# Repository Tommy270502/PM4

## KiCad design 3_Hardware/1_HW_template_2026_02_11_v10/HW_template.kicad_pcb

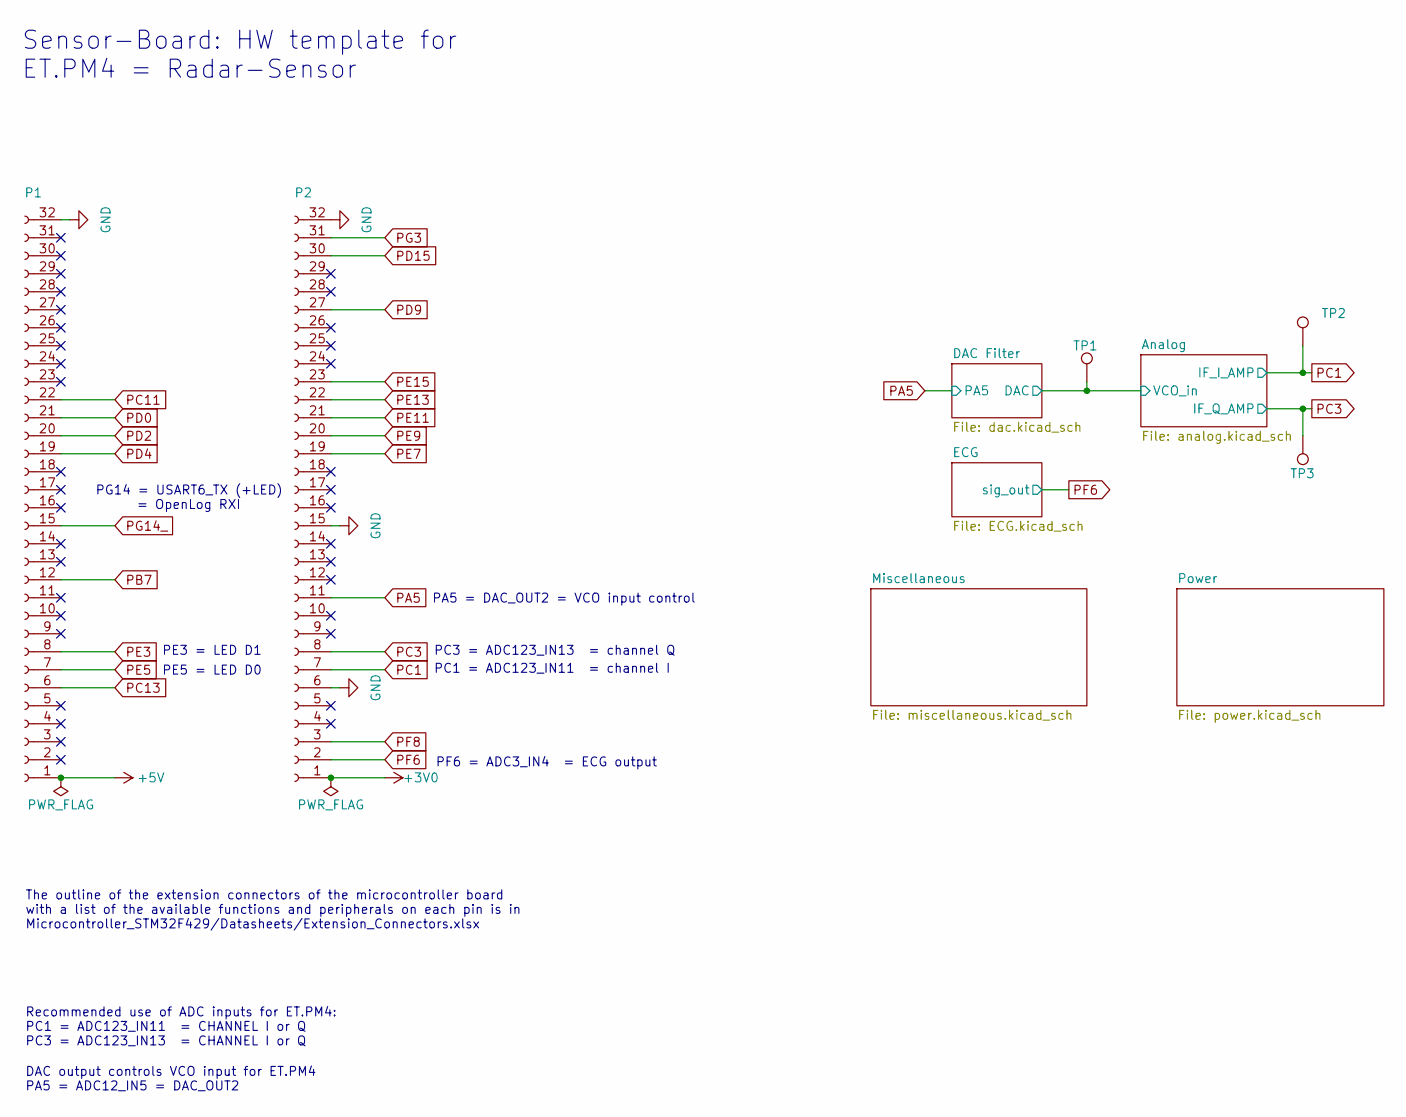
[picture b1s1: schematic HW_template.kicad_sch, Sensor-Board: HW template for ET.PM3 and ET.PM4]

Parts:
P1, P2: Conn_01x32_Female; PinSocket_1x32_P2.54mm_Vertical
TP1, TP2, TP3: TestPoint_Loop_D2.60mm_Drill1.6mm_Beaded

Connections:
+3V0: P2.1
+5V: P1.1; also elsewhere on the board
/Analog/VCO_in: TP1.1; also elsewhere on the board
GND: P1.32, P2.6, P2.15, P2.32; also elsewhere on the board
PA5: P2.11; also elsewhere on the board
PB7: P1.12
PC1: P2.7, TP2.1; also elsewhere on the board
PC3: P2.8, TP3.1; also elsewhere on the board
PC11: P1.22
PC13: P1.6
PD0: P1.21
PD2: P1.20
PD4: P1.19
PD9: P2.27
PD15: P2.30
PE3: P1.8; also elsewhere on the board
PE5: P1.7; also elsewhere on the board
PE7: P2.19
PE9: P2.20
PE11: P2.21
PE13: P2.22
PE15: P2.23
PF6: P2.2; also elsewhere on the board
PF8: P2.3
PG3: P2.31
PG14_: P1.15; also elsewhere on the board

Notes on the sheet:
The outline of the extension connectors of the microcontroller board with a list of the available functions and peripherals on each pin is in Microcontroller_STM32F429/Datasheets/Extension_Connectors.xlsx
PA5 = DAC_OUT2 = VCO input control
PG14 = USART6_TX (+LED) = OpenLog RXI
PC3 = ADC123_IN13 = channel Q
DAC output controls VCO input for ET.PM4 PA5 = ADC12_IN5 = DAC_OUT2
PF6 = ADC3_IN4 = ECG output
PE5 = LED D0
Recommended use of ADC inputs for ET.PM4: PC1 = ADC123_IN11 = CHANNEL I or Q PC3 = ADC123_IN13 = CHANNEL I or Q
PC1 = ADC123_IN11 = channel I
Sensor-Board: HW template for ET.PM4 = Radar-Sensor
PE3 = LED D1

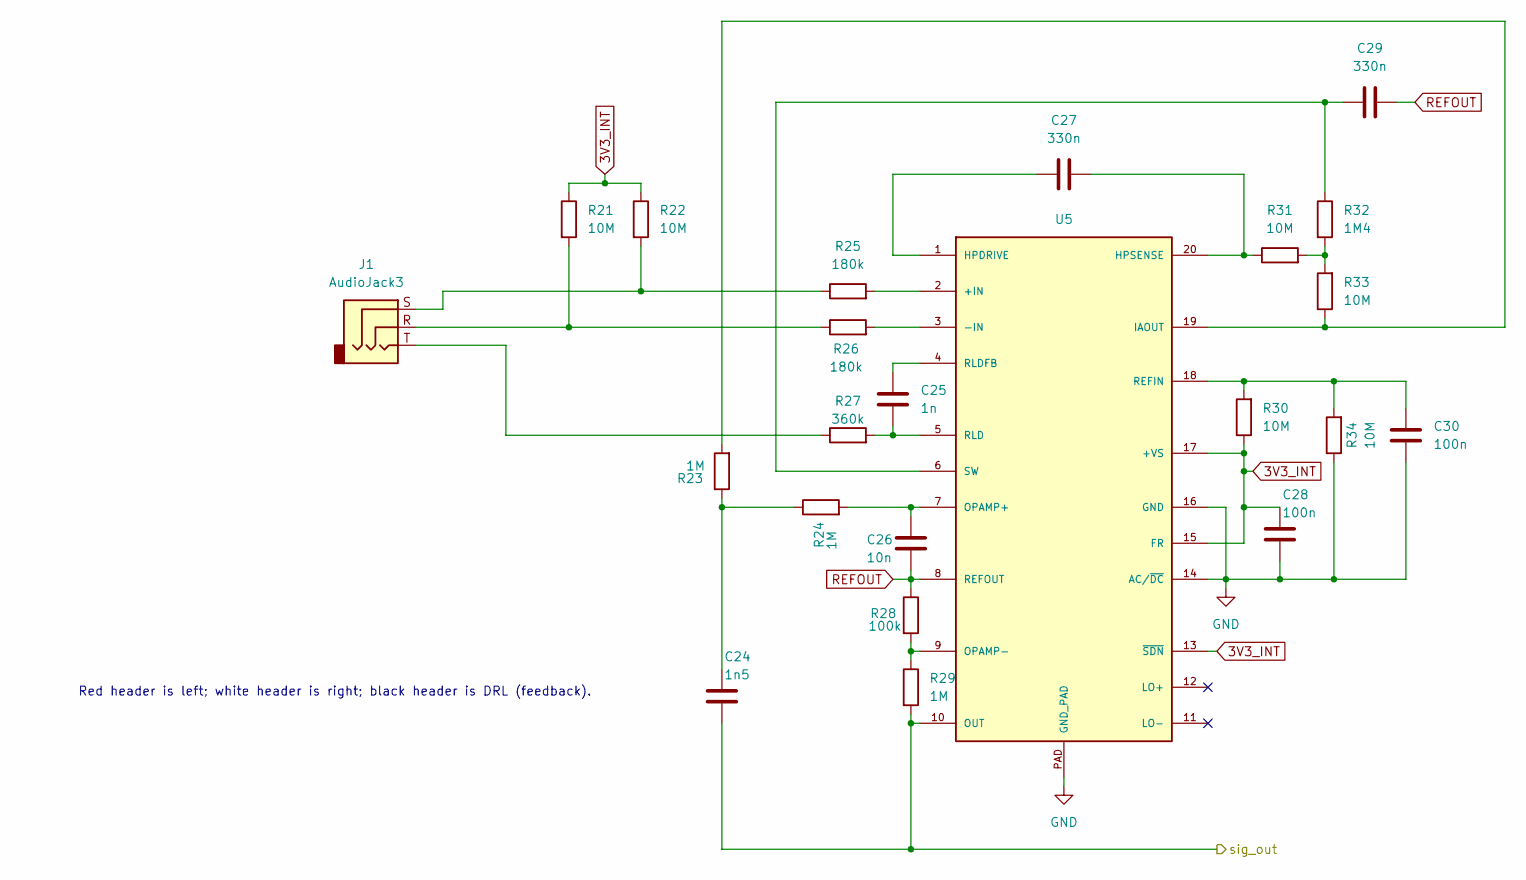
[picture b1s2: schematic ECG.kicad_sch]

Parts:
C24: 1n5; C_0603_1608Metric_Pad1.08x0.95mm_HandSolder
C25: 1n; C_0603_1608Metric_Pad1.08x0.95mm_HandSolder
C26: 10n; C_0603_1608Metric_Pad1.08x0.95mm_HandSolder
C27, C29: 330n; C_0603_1608Metric_Pad1.08x0.95mm_HandSolder
C28, C30: 100n; C_0603_1608Metric_Pad1.08x0.95mm_HandSolder
J1: AudioJack3; Jack_3.5mm_CUI_SJ-3523-SMT_Horizontal
R21, R22, R30, R31, R33, R34: 10M; R_0603_1608Metric_Pad0.98x0.95mm_HandSolder
R23, R24, R29: 1M; R_0603_1608Metric_Pad0.98x0.95mm_HandSolder
R25, R26: 180k; R_0603_1608Metric_Pad0.98x0.95mm_HandSolder
R27: 360k; R_0603_1608Metric_Pad0.98x0.95mm_HandSolder
R28: 100k; R_0603_1608Metric_Pad0.98x0.95mm_HandSolder
R32: 1M4; R_0603_1608Metric_Pad0.98x0.95mm_HandSolder
U5: AD8232ACPZ-R7; LFCSP_20

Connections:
3V3_INT: C28.2, R21.1, R22.1, R30.1, U5.13 (~SDN), U5.15 (FR), U5.17 (+VS); also elsewhere on the board
GND: C28.1, C30.1, R34.1, U5.14 (AC/~DC), U5.16 (GND), U5.PAD (GND_PAD); also elsewhere on the board
unnamed: C24.2, R23.1, R24.1
unnamed: J1.R, R21.2, R26.1
unnamed: J1.S, R22.2, R25.1
unnamed: J1.T, R27.1
unnamed: R31.2, R32.2, R33.2
unnamed: R25.2, U5.2 (+IN)
unnamed: R26.2, U5.3 (-IN)
unnamed: C27.1, U5.1 (HPDRIVE)
unnamed: C27.2, R31.1, U5.20 (HPSENSE)
unnamed: R23.2, R33.1, U5.19 (IAOUT)
unnamed: C26.2, R24.2, U5.7 (OPAMP+)
unnamed: R28.2, R29.1, U5.9 (OPAMP-)
unnamed: C30.2, R30.2, R34.2, U5.18 (REFIN)
unnamed: C25.2, R27.2, U5.5 (RLD)
unnamed: C25.1, U5.4 (RLDFB)
unnamed: C29.1, R32.1, U5.6 (SW)
PF6: C24.1, R29.2, U5.10 (OUT); also elsewhere on the board
REFOUT: C26.1, C29.2, R28.1, U5.8 (REFOUT)

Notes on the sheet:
Red header is left; white header is right; black header is DRL (feedback).

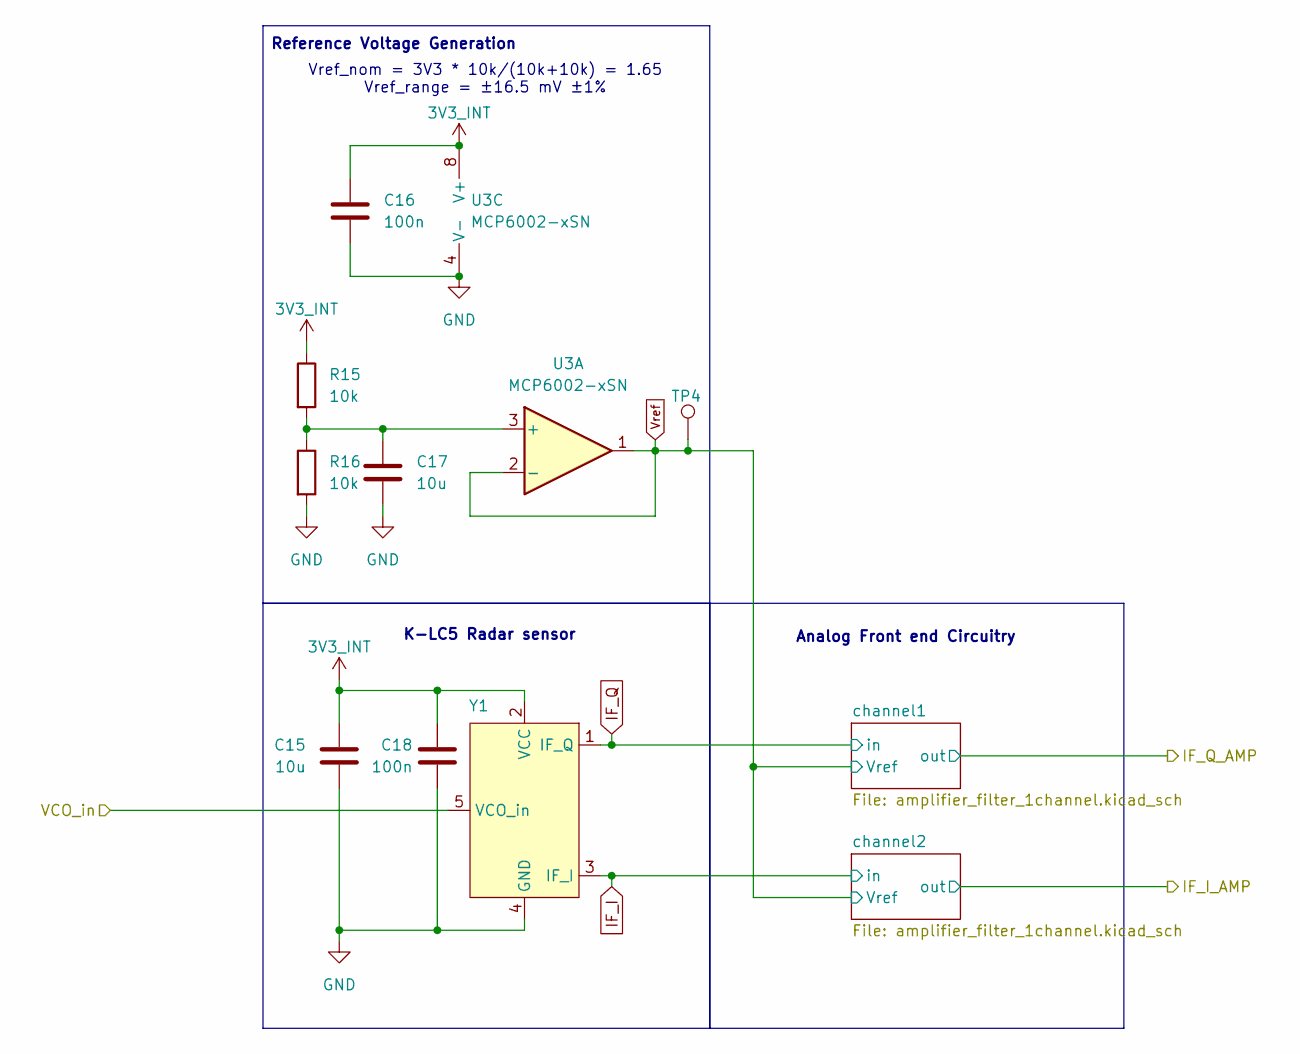
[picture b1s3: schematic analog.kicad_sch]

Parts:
C15, C17: 10u; C_0603_1608Metric_Pad1.08x0.95mm_HandSolder
C16, C18: 100n; C_0603_1608Metric_Pad1.08x0.95mm_HandSolder
R15, R16: 10k; R_0603_1608Metric_Pad0.98x0.95mm_HandSolder
TP4: TestPoint_Loop_D2.60mm_Drill1.6mm_Beaded
U3: MCP6002-xSN; SOIC-8_3.9x4.9mm_P1.27mm
Y1: Radar K-LC5-RFB-00C; Radar_K-LC5

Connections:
3V3_INT: C15.1, C16.1, C18.1, R15.1, U3.8 (V+), Y1.2 (VCC); also elsewhere on the board
/Analog/VCO_in: Y1.5 (VCO_in); also elsewhere on the board
GND: C15.2, C16.2, C17.2, C18.2, R16.2, U3.4 (V-), Y1.4 (GND); also elsewhere on the board
IF_I: Y1.3 (IF_I); also elsewhere on the board
IF_Q: Y1.1 (IF_Q); also elsewhere on the board
unnamed: C17.1, R15.2, R16.1, U3.3 (+)
Vref: TP4.1, U3.1, U3.2 (-); also elsewhere on the board

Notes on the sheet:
Analog Front end Circuitry
Reference Voltage Generation
K-LC5 Radar sensor
Vref_nom = 3V3 * 10k/(10k+10k) = 1.65 Vref_range = ±16.5 mV ±1%

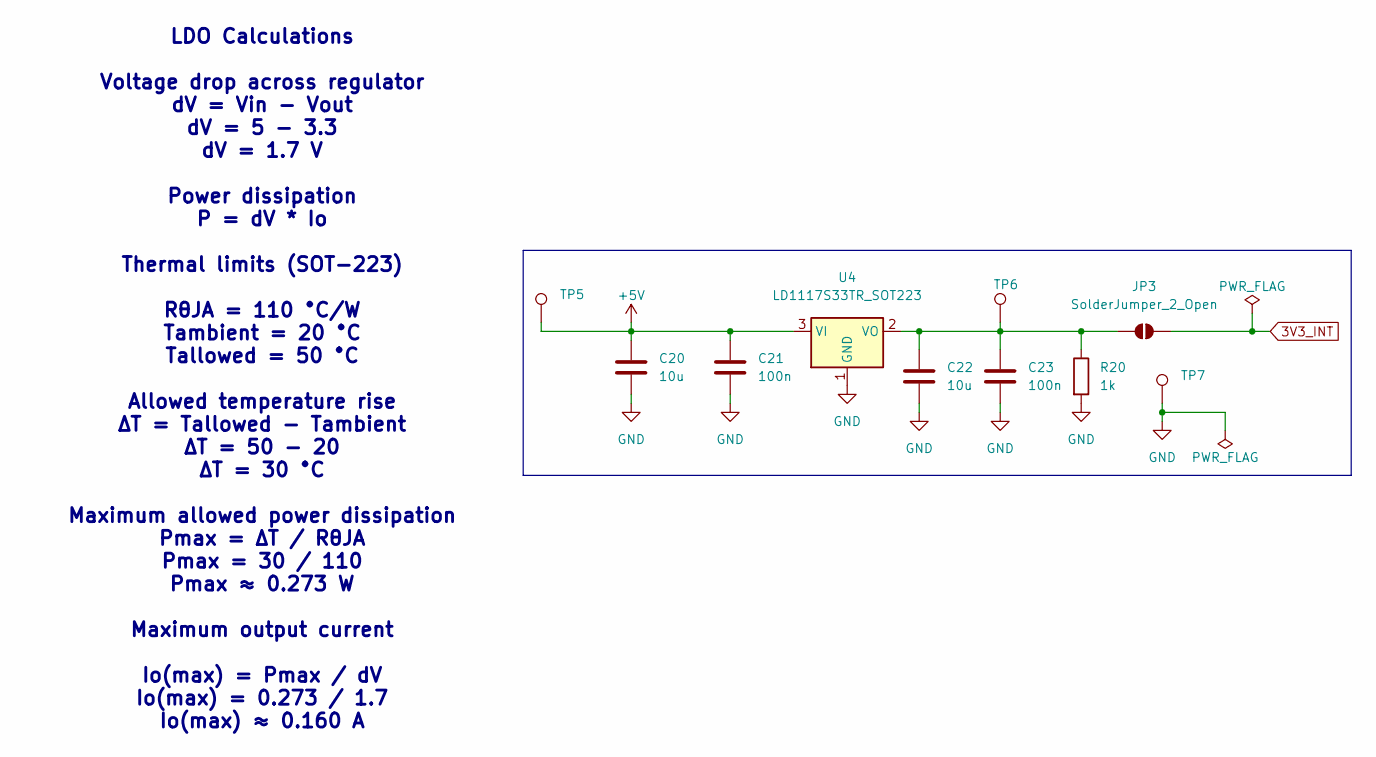
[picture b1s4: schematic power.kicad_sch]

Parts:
C20, C22: 10u; C_0805_2012Metric_Pad1.18x1.45mm_HandSolder
C21, C23: 100n; C_0805_2012Metric_Pad1.18x1.45mm_HandSolder
JP3: SolderJumper_2_Open; SolderJumper-2_P1.3mm_Open_RoundedPad1.0x1.5mm
R20: 1k; R_0805_2012Metric_Pad1.20x1.40mm_HandSolder
TP5, TP6, TP7: TestPoint_Loop_D2.60mm_Drill1.6mm_Beaded
U4: LD1117S33TR_SOT223; SOT-223-3_TabPin2

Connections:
3V3_INT: JP3.2 (B); also elsewhere on the board
+5V: C20.1, C21.1, TP5.1, U4.3 (VI); also elsewhere on the board
GND: C20.2, C21.2, C22.2, C23.2, R20.2, TP7.1, U4.1 (GND); also elsewhere on the board
unnamed: C22.1, C23.1, JP3.1 (A), R20.1, TP6.1, U4.2 (VO)

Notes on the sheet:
LDO Calculations Voltage drop across regulator dV = Vin - Vout dV = 5 - 3.3 dV = 1.7 V Power dissipation P = dV * Io Thermal limits (SOT-223) RθJA = 110 °C/W Tambient = 20 °C Tallowed = 50 °C Allowed temperature rise ΔT = Tallowed - Tambient ΔT = 50 - 20 ΔT = 30 °C Maximum allowed power dissipation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

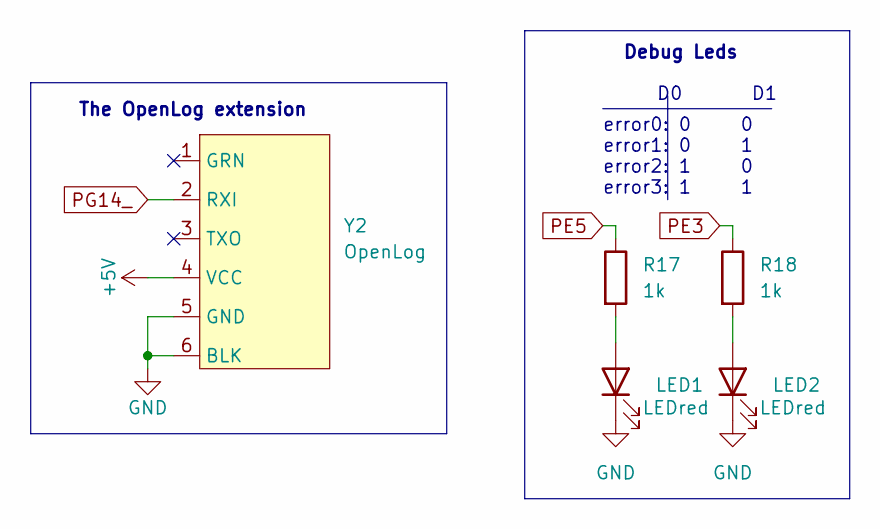
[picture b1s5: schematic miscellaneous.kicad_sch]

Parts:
LED1, LED2: LEDred; LED_0603_1608Metric_Pad1.05x0.95mm_HandSolder
R17, R18: 1k; R_0603_1608Metric_Pad0.98x0.95mm_HandSolder
Y2: OpenLog; PinSocket_1x06_P2.54mm_Vertical

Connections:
+5V: Y2.4 (VCC); also elsewhere on the board
GND: LED1.1 (K), LED2.1 (K), Y2.5 (GND), Y2.6 (BLK); also elsewhere on the board
unnamed: LED1.2 (A), R17.2
unnamed: LED2.2 (A), R18.2
PE3: R18.1; also elsewhere on the board
PE5: R17.1; also elsewhere on the board
PG14_: Y2.2 (RXI); also elsewhere on the board

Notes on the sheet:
error0: 0 0 error1: 0 1 error2: 1 0 error3: 1 1
The OpenLog extension
D0 D1
Debug Leds

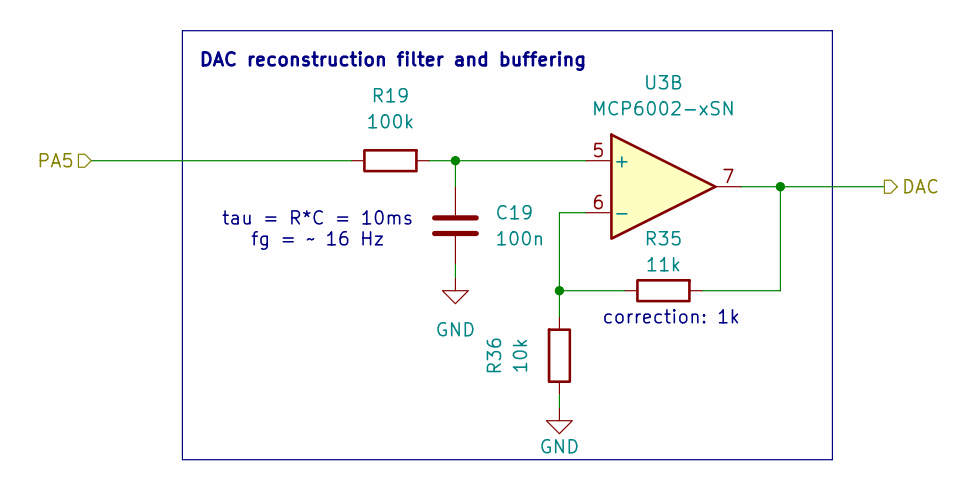
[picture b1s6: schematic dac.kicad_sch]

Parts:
C19: 100n; C_0603_1608Metric_Pad1.08x0.95mm_HandSolder
R19: 100k; R_0603_1608Metric_Pad0.98x0.95mm_HandSolder
R35: 11k; R_0603_1608Metric_Pad0.98x0.95mm_HandSolder
R36: 10k; R_0603_1608Metric_Pad0.98x0.95mm_HandSolder
U3: MCP6002-xSN; SOIC-8_3.9x4.9mm_P1.27mm

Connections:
/Analog/VCO_in: R35.2, U3.7; also elsewhere on the board
GND: C19.2, R36.1; also elsewhere on the board
unnamed: C19.1, R19.2, U3.5 (+)
unnamed: R35.1, R36.2, U3.6 (-)
PA5: R19.1; also elsewhere on the board

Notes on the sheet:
DAC reconstruction filter and buffering
correction: 1k
tau = R*C = 10ms fg = ~ 16 Hz

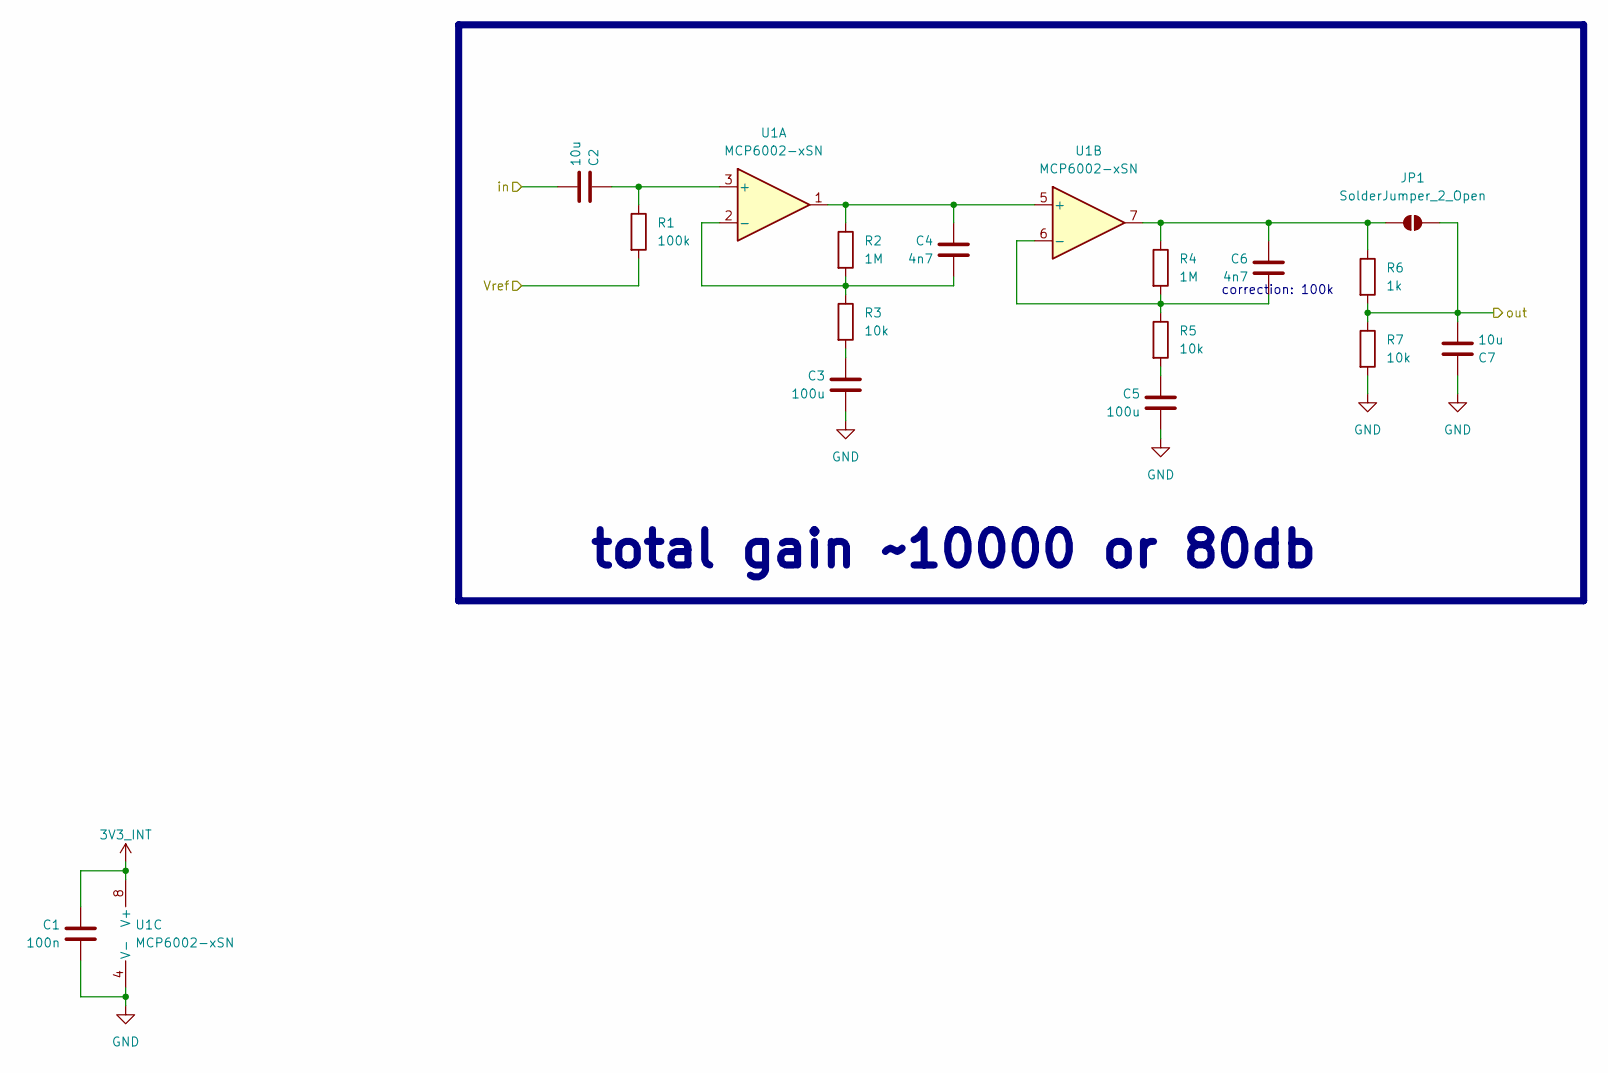
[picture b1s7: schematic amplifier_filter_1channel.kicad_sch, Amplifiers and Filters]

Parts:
C1: 100n; C_0603_1608Metric_Pad1.08x0.95mm_HandSolder
C2, C7: 10u; C_0603_1608Metric_Pad1.08x0.95mm_HandSolder
C3, C5: 100u; C_1206_3216Metric_Pad1.33x1.80mm_HandSolder
C4, C6: 4n7; C_0603_1608Metric_Pad1.08x0.95mm_HandSolder
JP1: SolderJumper_2_Open; SolderJumper-2_P1.3mm_Open_RoundedPad1.0x1.5mm
R1: 100k; R_0603_1608Metric_Pad0.98x0.95mm_HandSolder
R2, R4: 1M; R_0603_1608Metric_Pad0.98x0.95mm_HandSolder
R3, R5, R7: 10k; R_0603_1608Metric_Pad0.98x0.95mm_HandSolder
R6: 1k; R_0603_1608Metric_Pad0.98x0.95mm_HandSolder
U1: MCP6002-xSN; SOIC-8_3.9x4.9mm_P1.27mm

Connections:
3V3_INT: C1.1, U1.8 (V+); also elsewhere on the board
GND: C1.2, C3.2, C5.2, C7.1, R7.2, U1.4 (V-); also elsewhere on the board
IF_Q: C2.2; also elsewhere on the board
unnamed: C3.1, R3.2
unnamed: C5.1, R5.2
unnamed: C6.1, JP1.1 (A), R4.1, R6.1, U1.7
unnamed: C2.1, R1.1, U1.3 (+)
unnamed: C4.2, R2.2, R3.1, U1.2 (-)
unnamed: C4.1, R2.1, U1.1, U1.5 (+)
unnamed: C6.2, R4.2, R5.1, U1.6 (-)
PC3: C7.2, JP1.2 (B), R6.2, R7.1; also elsewhere on the board
Vref: R1.2; also elsewhere on the board

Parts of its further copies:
C8: 100n; C_0603_1608Metric_Pad1.08x0.95mm_HandSolder
C9, C14: 10u; C_0603_1608Metric_Pad1.08x0.95mm_HandSolder
C10, C12: 100u; C_1206_3216Metric_Pad1.33x1.80mm_HandSolder
C11, C13: 4n7; C_0603_1608Metric_Pad1.08x0.95mm_HandSolder
JP2: SolderJumper_2_Open; SolderJumper-2_P1.3mm_Open_RoundedPad1.0x1.5mm
R8: 100k; R_0603_1608Metric_Pad0.98x0.95mm_HandSolder
R9, R11: 1M; R_0603_1608Metric_Pad0.98x0.95mm_HandSolder
R10, R12, R14: 10k; R_0603_1608Metric_Pad0.98x0.95mm_HandSolder
R13: 1k; R_0603_1608Metric_Pad0.98x0.95mm_HandSolder
U2: MCP6002-xSN; SOIC-8_3.9x4.9mm_P1.27mm

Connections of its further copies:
3V3_INT: C8.1, U2.8 (V+); also elsewhere on the board
GND: C8.2, C10.2, C12.2, C14.1, R14.2, U2.4 (V-); also elsewhere on the board
IF_I: C9.2; also elsewhere on the board
unnamed: C10.1, R10.2
unnamed: C12.1, R12.2
unnamed: C13.1, JP2.1 (A), R11.1, R13.1, U2.7
unnamed: C9.1, R8.1, U2.3 (+)
unnamed: C11.2, R9.2, R10.1, U2.2 (-)
unnamed: C11.1, R9.1, U2.1, U2.5 (+)
unnamed: C13.2, R11.2, R12.1, U2.6 (-)
PC1: C14.2, JP2.2 (B), R13.2, R14.1; also elsewhere on the board
Vref: R8.2; also elsewhere on the board

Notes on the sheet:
correction: 100k
total gain ~10000 or 80db

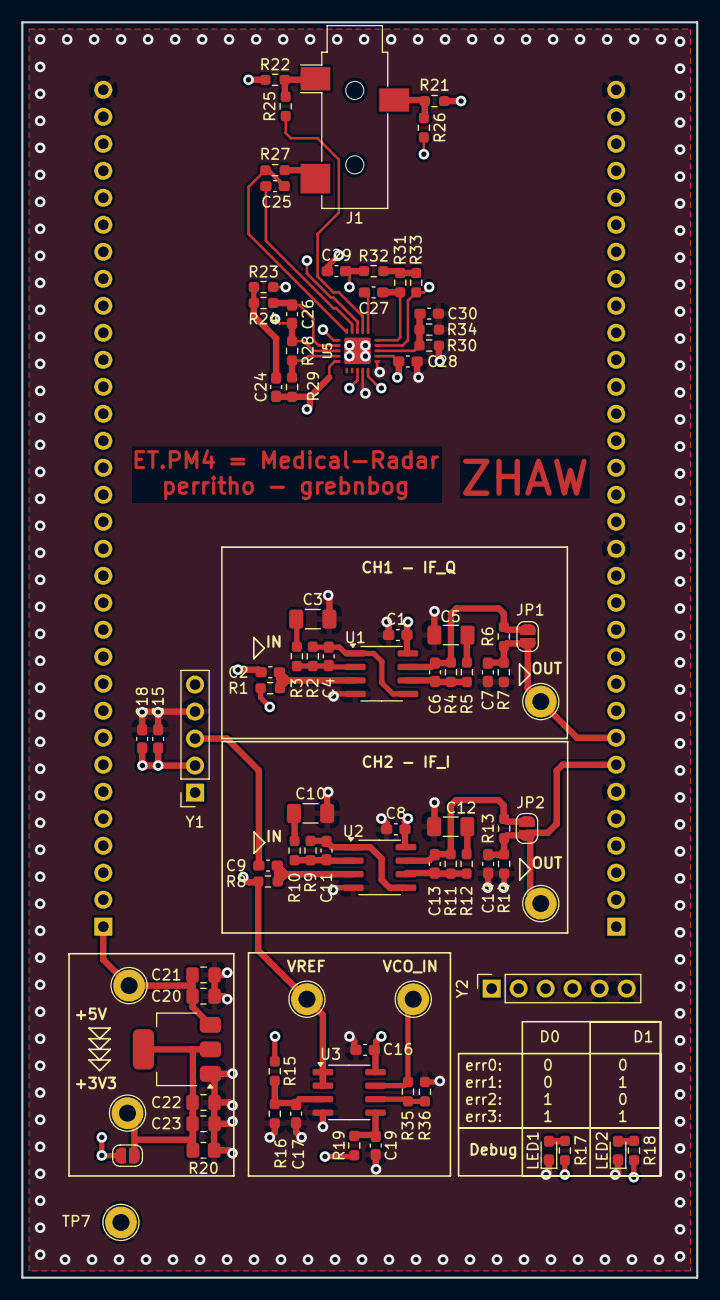
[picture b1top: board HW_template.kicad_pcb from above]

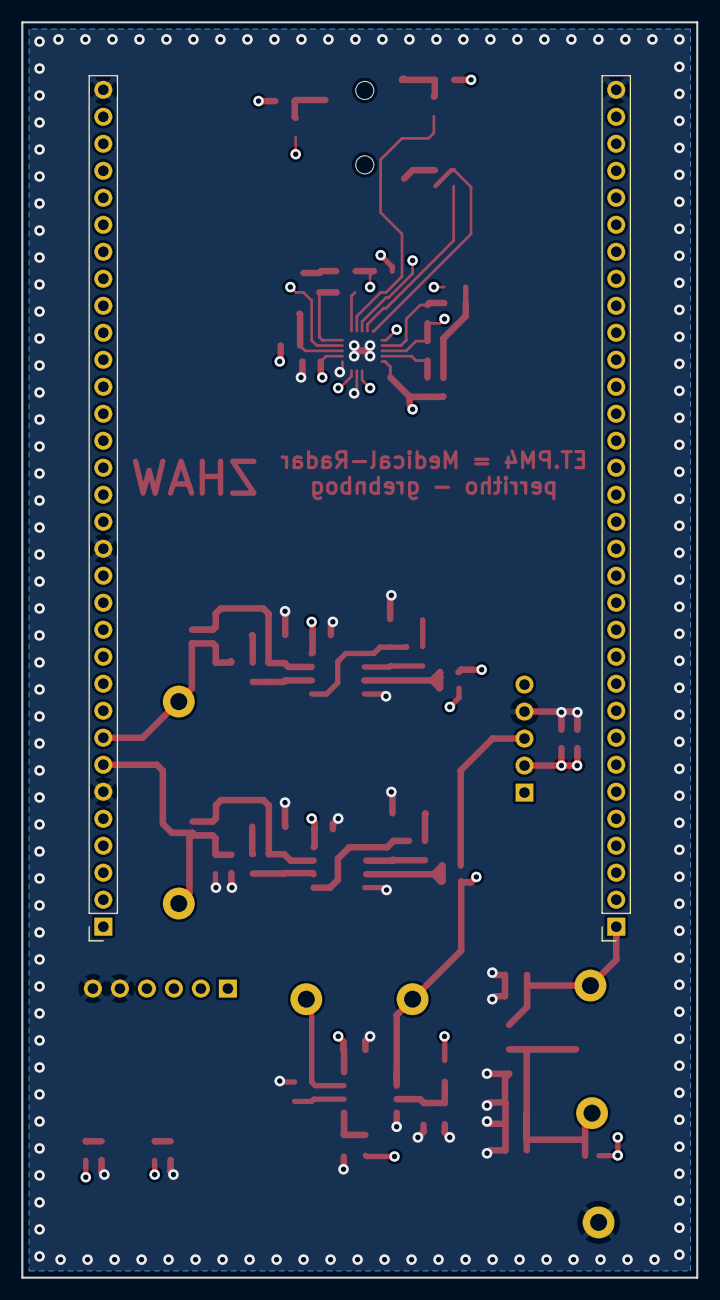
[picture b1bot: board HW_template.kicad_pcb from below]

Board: 4 copper layers, 63.5 x 118.1 mm, 88 parts (2 on the bottom side), 51 nets.

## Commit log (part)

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2026-02-19 added project files
2026-02-19 Track mp4 files with Git LFS
2026-02-19 Remove large video file
2026-02-19 hardware template unzipped
2026-02-19 added radar analog front end application note
2026-02-19 firmware template unzipped
2026-02-26 removed timeline for another class
2026-02-26 added vco amplifier simulation
2026-02-26 removed .ds files
2026-02-26 updated gitignore
2026-02-26 onepager - wip
2026-02-26 added cheaper analog frontend circuitry simulation
2026-02-26 improved amplification
2026-02-26 added some more IF_amp designs
2026-02-26 Ignore .raw artifacts
2026-02-26 first analog circuitry implemented in kicad
2026-03-05 added amp filter v5
2026-03-05 added analysis
2026-03-08 added eand design
2026-03-08 finalize main feature
2026-03-11 layout template
2026-03-11 added AD8232
2026-03-11 added ecg schematic and part list to order
2026-03-12 onepager final
2026-03-12 updated parts order excel version
2026-03-12 onepager minor update
2026-03-12 added datasheet and started layout
2026-03-12 parts order updated with cheaper cables for ECG
2026-03-12 disabled excel automatic backup
2026-03-12 updated layout
2026-03-12 standard component list
2026-03-12 onepager final after review
2026-03-12 converted some pdfs to markdown
2026-03-12 simulations
2026-03-18 pcb schematics finished + layout
2026-03-18 layout finished + component libs updated
2026-03-19 updated materials on fft implementation
2026-03-19 pcb - minor naming improvements
2026-03-19 fixed footprints
2026-03-19 designed pcb
2026-03-19 finalized pcb
2026-03-19 component order form updated
2026-03-19 minor pcb improvements + bom
2026-03-19 pcb minor improvements
2026-03-19 added amplification to VCO
2026-03-19 gerber
2026-03-19 component order form (capacitors) + bom
2026-03-19 finalized component order form
2026-03-19 order finalization
2026-03-25 firmware agentic implementation (old version)
2026-03-26 replaced firmware template
2026-03-26 firmware agent guidlines (old version)
2026-03-26 firmware agent guidlines (new version)
2026-03-26 ai implementation
2026-03-26 firmware agent guidlines moved
2026-03-26 pm3 code base
2026-03-26 dmx removed
2026-03-26 i2s audio input removed
2026-03-26 firmware overview generic version
2026-03-26 fixed c project for me
2026-03-26 started with changes for radar data
2026-03-26 removed mirror channel function
2026-03-26 ekg.c & ekg.h
2026-03-26 implemented ekg
2026-03-26 removed unnecessary code
2026-03-26 minimum working product
2026-03-26 variables renamed
2026-03-26 leftovers renamed
2026-03-26 renamed files
2026-03-26 renamed CubeIDE project
2026-03-26 renamed calc -> fft
2026-03-26 removed light bar menu
2026-03-26 added docstring to ekg
2026-03-26 centered frequency spectrum and modified time scale
2026-03-26 fixed fft scaling and time signal scaling, also did 50% overlap on samples rolling 512 sample window but all 2.56s 256 new samples
2026-03-27 added dac control
2026-04-02 requirements updated for subsystem tests
2026-04-02 simulation updated to match PCB
2026-04-02 vco amp simulation added
2026-04-02 vco error fixed: replaced 11k with 1k
2026-04-05 cleaned up some file
2026-04-05 fw test plan
2026-04-06 fw test plan updated
2026-04-06 fw test plan - minor improvements
2026-04-06 hw test plan
2026-04-06 hw test plan updated, first results added
2026-04-06 unnecessary template removed
2026-04-07 radar target manual added + invalid shortcut removed
2026-04-07 hw test plan radar-connected tests added
2026-04-07 hw block diagram
2026-04-09 hw block diagram - minor improvement
2026-04-09 pcb fix
2026-04-09 test plans updated + some results
2026-04-09 frequency readout added
2026-04-09 refactor 1
2026-04-09 refactor 2
2026-04-09 refactor 3
2026-04-09 refactor 4
2026-04-09 added c_cpp_properties.json to remove false warning
2026-04-16 ft test plan minor updates
2026-04-16 frequncy peak redout improved
2026-04-16 added firmware architecture diagrams
2026-04-16 fw test passed
2026-04-16 fw block diagram moved and renamed
2026-04-16 simulation updated
2026-04-16 hw test passed
2026-04-16 subsystem test reports as PDF
2026-04-22 made videopresentationscript.md
2026-04-22 generated pdf
2026-04-22 updated marks excel
2026-04-22 pcb 3d model
2026-04-22 doing mechanical work for the casing
2026-04-22 got base measurements from pcb but missing devboard headerheight
2026-04-23 flipped LCD display
2026-04-23 part order list
2026-04-23 removed firmware template
2026-04-23 outdated fw overview removed
2026-04-23 heart rate estimation algorithm v1
2026-04-23 removed .pdf_build directory
2026-04-23 updated video script pdf + modified script to autoremove build directory
2026-04-23 minor plan improvement
2026-04-23 heart rate detection implemented
2026-04-27 casing skeleton
2026-04-27 made base design
2026-04-27 made base better looking IMO and added a hole for feedthrough of usb cable
2026-04-27 minor looks
2026-04-27 lowered center of mass
2026-04-30 minor video script improvements
2026-04-30 vidoe script file renamed
2026-04-30 video script v2
2026-05-07 files updated
2026-05-08 copied template for powerpoint
2026-05-08 presentation wip
2026-05-11 stimmgabel V2
2026-05-11 removed digital filter for ekg as the analog frontend already does this
2026-05-15 minor script adjustments
2026-05-15 images added
2026-05-16 some more images
2026-05-16 tuned ekg config (to be tested)
2026-05-17 rotated display
2026-05-17 Refactor radar acquisition and add displacement-based HR input
    - shorten radar DMA ISR to only publish completed buffer metadata
    - move I/Q unpacking and rolling-window updates to foreground code
    - add radar DMA sequence, overrun, and error counters
    - add I/Q phase unwrap and displacement conversion path
    - add phase quality flags for clipping and low signal conditions
    - feed radar HR estimator from displacement FFT instead of I/Q magnitude FFT
2026-05-17 EKG works perfectly fine, Radar also better
2026-05-17 some cleanup
2026-05-18 lcd screenshots
2026-05-19 more images
2026-05-19 video script updated
2026-05-20 screenshots
2026-05-20 added firmware architecture and modified the videopresentationscript
2026-05-20 voiceover 02-04
2026-05-20 voiceover 09-12
2026-05-20 product pictures
2026-05-20 product showcase videos
2026-05-20 images
2026-05-21 ekg radar signal path
2026-05-21 more pictures
2026-05-21 data logger 3d files
2026-05-21 inserted data logger 3d model in hw
2026-05-21 pictures
2026-05-21 voicecovers
2026-05-21 shortened script
2026-05-21 presentation wip + images
2026-05-21 folie 11 voiceover
2026-05-21 folie 12 voiceover
2026-05-21 image, voicover
2026-05-21 presentation (final?)
2026-05-21 video
2026-05-21 added ekg time signal
2026-05-21 PM4 final video
2026-06-02 marks excel updated
2026-06-22 added measurment logging data
2026-06-22 added plot for log data
